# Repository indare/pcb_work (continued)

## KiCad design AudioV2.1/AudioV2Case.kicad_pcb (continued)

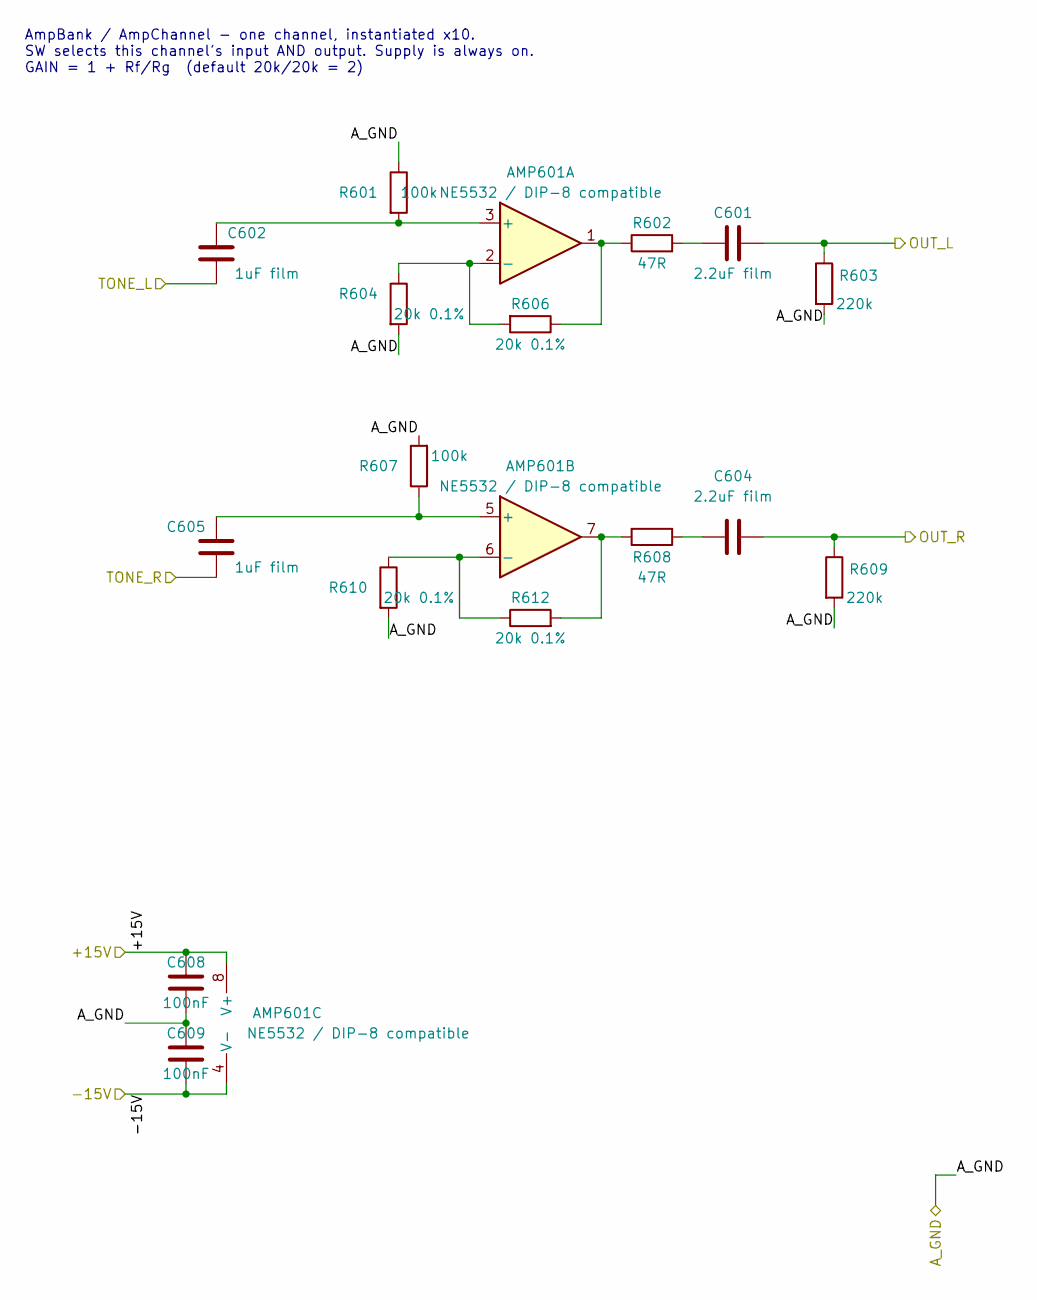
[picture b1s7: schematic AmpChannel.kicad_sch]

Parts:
AMP601: NE5532 / DIP-8 compatible; DIP-8_W7.62mm_Socket
C601, C604: 2.2uF film; C_Rect_L7.2mm_W7.2mm_P5.00mm_FKS2_FKP2_MKS2_MKP2
C602, C605: 1uF film; C_Rect_L7.2mm_W4.5mm_P5.00mm_FKS2_FKP2_MKS2_MKP2
C608, C609: 100nF; C_1206_3216Metric_Pad1.33x1.80mm_HandSolder
R601, R607: 100k; R_1206_3216Metric_Pad1.30x1.75mm_HandSolder
R602, R608: 47R; R_1206_3216Metric_Pad1.30x1.75mm_HandSolder
R603, R609: 220k; R_1206_3216Metric_Pad1.30x1.75mm_HandSolder
R604, R606, R610, R612: 20k 0.1%; R_0805_2012Metric_Pad1.20x1.40mm_HandSolder

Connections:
/+15V: AMP601.8 (V+), C608.1; also elsewhere on the board
/-15V: AMP601.4 (V-), C609.2; also elsewhere on the board
/A_GND: C608.2, C609.1, R601.1, R603.2, R604.2, R607.2, R609.2, R610.2; also elsewhere on the board
/AmpBankSwitch/CH1_OUT_L: C601.2, R603.1; also elsewhere on the board
/AmpBankSwitch/CH1_OUT_R: C604.1, R609.1; also elsewhere on the board
/TONE_L: C602.1; also elsewhere on the board
/TONE_R: C605.1; also elsewhere on the board
unnamed: AMP601.1, R602.1, R606.1
unnamed: AMP601.7, R608.2, R612.2
unnamed: AMP601.3 (+), C602.2, R601.2
unnamed: AMP601.2 (-), R604.1, R606.2
unnamed: AMP601.5 (+), C605.2, R607.1
unnamed: AMP601.6 (-), R610.1, R612.1
unnamed: C601.1, R602.2
unnamed: C604.2, R608.1

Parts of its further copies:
AMP701, AMP801, AMP901, AMP1001, AMP1101, AMP1201, AMP1301: NE5532 / DIP-8 compatible; DIP-8_W7.62mm_Socket
C701, C704, C801, C804, C901, C904, C1001, C1004, C1101, C1104, C1201, C1204, C1301, C1304: 2.2uF film; C_Rect_L7.2mm_W7.2mm_P5.00mm_FKS2_FKP2_MKS2_MKP2
C702, C705, C802, C805, C902, C905, C1002, C1005, C1102, C1105, C1202, C1205, C1302, C1305: 1uF film; C_Rect_L7.2mm_W4.5mm_P5.00mm_FKS2_FKP2_MKS2_MKP2
C708, C709, C808, C809, C908, C909, C1008, C1009, C1108, C1109, C1208, C1209, C1308, C1309: 100nF; C_1206_3216Metric_Pad1.33x1.80mm_HandSolder
R701, R707, R801, R807, R901, R907, R1001, R1007, R1101, R1107, R1201, R1207, R1301, R1307: 100k; R_1206_3216Metric_Pad1.30x1.75mm_HandSolder
R702, R708, R802, R808, R902, R908, R1002, R1008, R1102, R1108, R1202, R1208, R1302, R1308: 47R; R_1206_3216Metric_Pad1.30x1.75mm_HandSolder
R703, R709, R803, R809, R903, R909, R1003, R1009, R1103, R1109, R1203, R1209, R1303, R1309: 220k; R_1206_3216Metric_Pad1.30x1.75mm_HandSolder
R704, R706, R710, R712, R804, R806, R810, R812, R904, R906, R910, R912, R1004, R1006, R1010, R1012, R1104, R1106, R1110, R1112, R1204, R1206, R1210, R1212, R1304, R1306, R1310, R1312: 20k 0.1%; R_0805_2012Metric_Pad1.20x1.40mm_HandSolder

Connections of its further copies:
/+15V: AMP701.8 (V+), AMP801.8 (V+), AMP901.8 (V+), AMP1001.8 (V+), AMP1101.8 (V+), AMP1201.8 (V+), AMP1301.8 (V+), C708.1, C808.1, C908.1, C1008.1, C1108.1, C1208.1, C1308.1; also elsewhere on the board
/-15V: AMP701.4 (V-), AMP801.4 (V-), AMP901.4 (V-), AMP1001.4 (V-), AMP1101.4 (V-), AMP1201.4 (V-), AMP1301.4 (V-), C709.2, C809.2, C909.2, C1009.2, C1109.2, C1209.2, C1309.2; also elsewhere on the board
/A_GND: C708.2, C709.1, C808.2, C809.1, C908.2, C909.1, C1008.2, C1009.1, C1108.2, C1109.1, C1208.2, C1209.1, C1308.2, C1309.1, R701.1, R703.2, R704.2, R707.2, R709.2, R710.2, R801.1, R803.2, R804.2, R807.2, R809.2, R810.2, R901.1, R903.2, R904.2, R907.2, R909.2, R910.2, R1001.1, R1003.2, R1004.2, R1007.2, R1009.2, R1010.2, R1101.1, R1103.2, R1104.2, R1107.2, R1109.2, R1110.2, R1201.1, R1203.2, R1204.2, R1207.2, R1209.2, R1210.2, R1301.1, R1303.2, R1304.2, R1307.2, R1309.2, R1310.2; also elsewhere on the board
/AmpBankRelay/CH1_OUT_L: C1001.2, R1003.1; also elsewhere on the board
/AmpBankRelay/CH1_OUT_R: C1004.1, R1009.1; also elsewhere on the board
/AmpBankRelay/CH2_OUT_L: C1101.2, R1103.1; also elsewhere on the board
/AmpBankRelay/CH2_OUT_R: C1104.1, R1109.1; also elsewhere on the board
/AmpBankRelay/CH3_OUT_L: C1201.2, R1203.1; also elsewhere on the board
/AmpBankRelay/CH3_OUT_R: C1204.1, R1209.1; also elsewhere on the board
/AmpBankRelay/CH4_OUT_L: C1301.2, R1303.1; also elsewhere on the board
/AmpBankRelay/CH4_OUT_R: C1304.1, R1309.1; also elsewhere on the board
/AmpBankSwitch/CH2_OUT_L: C701.2, R703.1; also elsewhere on the board
/AmpBankSwitch/CH2_OUT_R: C704.1, R709.1; also elsewhere on the board
/AmpBankSwitch/CH3_OUT_L: C801.2, R803.1; also elsewhere on the board
/AmpBankSwitch/CH3_OUT_R: C804.1, R809.1; also elsewhere on the board
/AmpBankSwitch/CH4_OUT_L: C901.2, R903.1; also elsewhere on the board
/AmpBankSwitch/CH4_OUT_R: C904.1, R909.1; also elsewhere on the board
/TONE_L: C702.1, C802.1, C902.1, C1002.1, C1102.1, C1202.1, C1302.1; also elsewhere on the board
/TONE_R: C705.1, C805.1, C905.1, C1005.1, C1105.1, C1205.1, C1305.1; also elsewhere on the board
unnamed: AMP701.1, R702.1, R706.1
unnamed: AMP701.7, R708.2, R712.2
unnamed: AMP701.3 (+), C702.2, R701.2
unnamed: AMP701.2 (-), R704.1, R706.2
unnamed: AMP701.5 (+), C705.2, R707.1
unnamed: AMP701.6 (-), R710.1, R712.1
unnamed: AMP801.1, R802.1, R806.1
unnamed: AMP801.7, R808.2, R812.2
unnamed: AMP801.3 (+), C802.2, R801.2
unnamed: AMP801.2 (-), R804.1, R806.2
unnamed: AMP801.5 (+), C805.2, R807.1
unnamed: AMP801.6 (-), R810.1, R812.1
unnamed: AMP901.1, R902.1, R906.1
unnamed: AMP901.7, R908.2, R912.2
unnamed: AMP901.3 (+), C902.2, R901.2
unnamed: AMP901.2 (-), R904.1, R906.2
unnamed: AMP901.5 (+), C905.2, R907.1
unnamed: AMP901.6 (-), R910.1, R912.1
unnamed: AMP1001.1, R1002.1, R1006.1
unnamed: AMP1001.7, R1008.2, R1012.2
unnamed: AMP1001.3 (+), C1002.2, R1001.2
unnamed: AMP1001.2 (-), R1004.1, R1006.2
unnamed: AMP1001.5 (+), C1005.2, R1007.1
unnamed: AMP1001.6 (-), R1010.1, R1012.1
unnamed: AMP1101.1, R1102.1, R1106.1
unnamed: AMP1101.7, R1108.2, R1112.2
unnamed: AMP1101.3 (+), C1102.2, R1101.2
unnamed: AMP1101.2 (-), R1104.1, R1106.2
unnamed: AMP1101.5 (+), C1105.2, R1107.1
unnamed: AMP1101.6 (-), R1110.1, R1112.1
unnamed: AMP1201.1, R1202.1, R1206.1
unnamed: AMP1201.7, R1208.2, R1212.2
unnamed: AMP1201.3 (+), C1202.2, R1201.2
unnamed: AMP1201.2 (-), R1204.1, R1206.2
unnamed: AMP1201.5 (+), C1205.2, R1207.1
unnamed: AMP1201.6 (-), R1210.1, R1212.1
unnamed: AMP1301.1, R1302.1, R1306.1
unnamed: AMP1301.7, R1308.2, R1312.2
unnamed: AMP1301.3 (+), C1302.2, R1301.2
unnamed: AMP1301.2 (-), R1304.1, R1306.2
unnamed: AMP1301.5 (+), C1305.2, R1307.1
unnamed: AMP1301.6 (-), R1310.1, R1312.1
unnamed: C701.1, R702.2
unnamed: C704.2, R708.1
unnamed: C801.1, R802.2
unnamed: C804.2, R808.1
unnamed: C901.1, R902.2
unnamed: C904.2, R908.1
unnamed: C1001.1, R1002.2
unnamed: C1004.2, R1008.1
unnamed: C1101.1, R1102.2
unnamed: C1104.2, R1108.1
unnamed: C1201.1, R1202.2
unnamed: C1204.2, R1208.1
unnamed: C1301.1, R1302.2
unnamed: C1304.2, R1308.1

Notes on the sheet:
AmpBank / AmpChannel - one channel, instantiated x10. SW selects this channel's input AND output. Supply is always on. GAIN = 1 + Rf/Rg (default 20k/20k = 2)

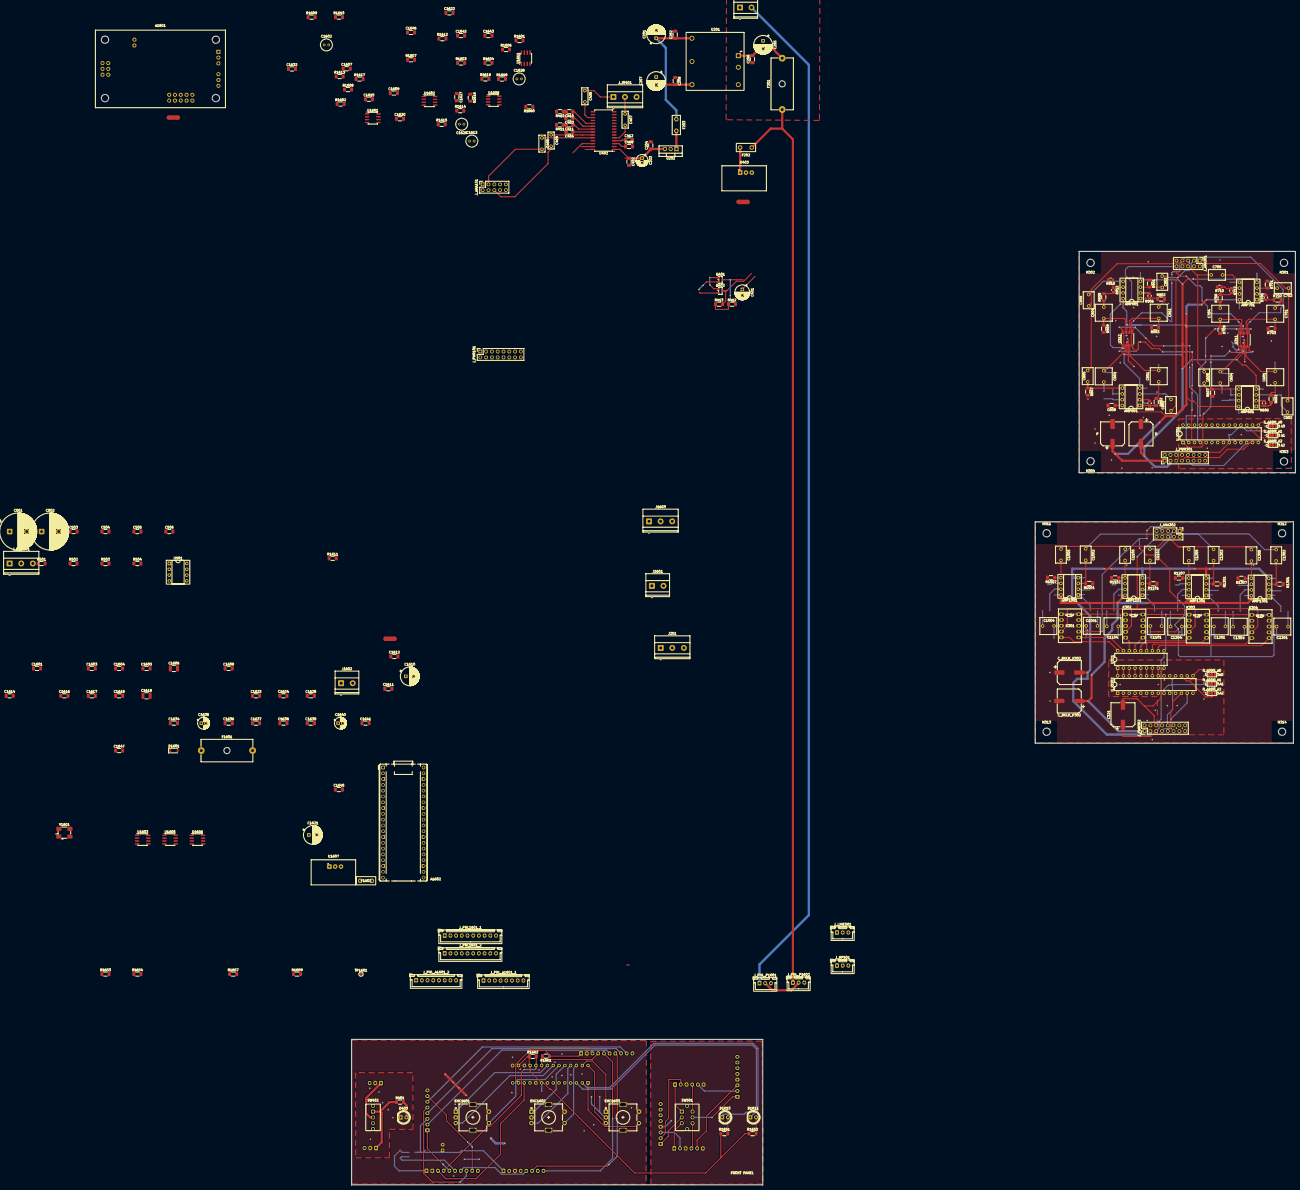
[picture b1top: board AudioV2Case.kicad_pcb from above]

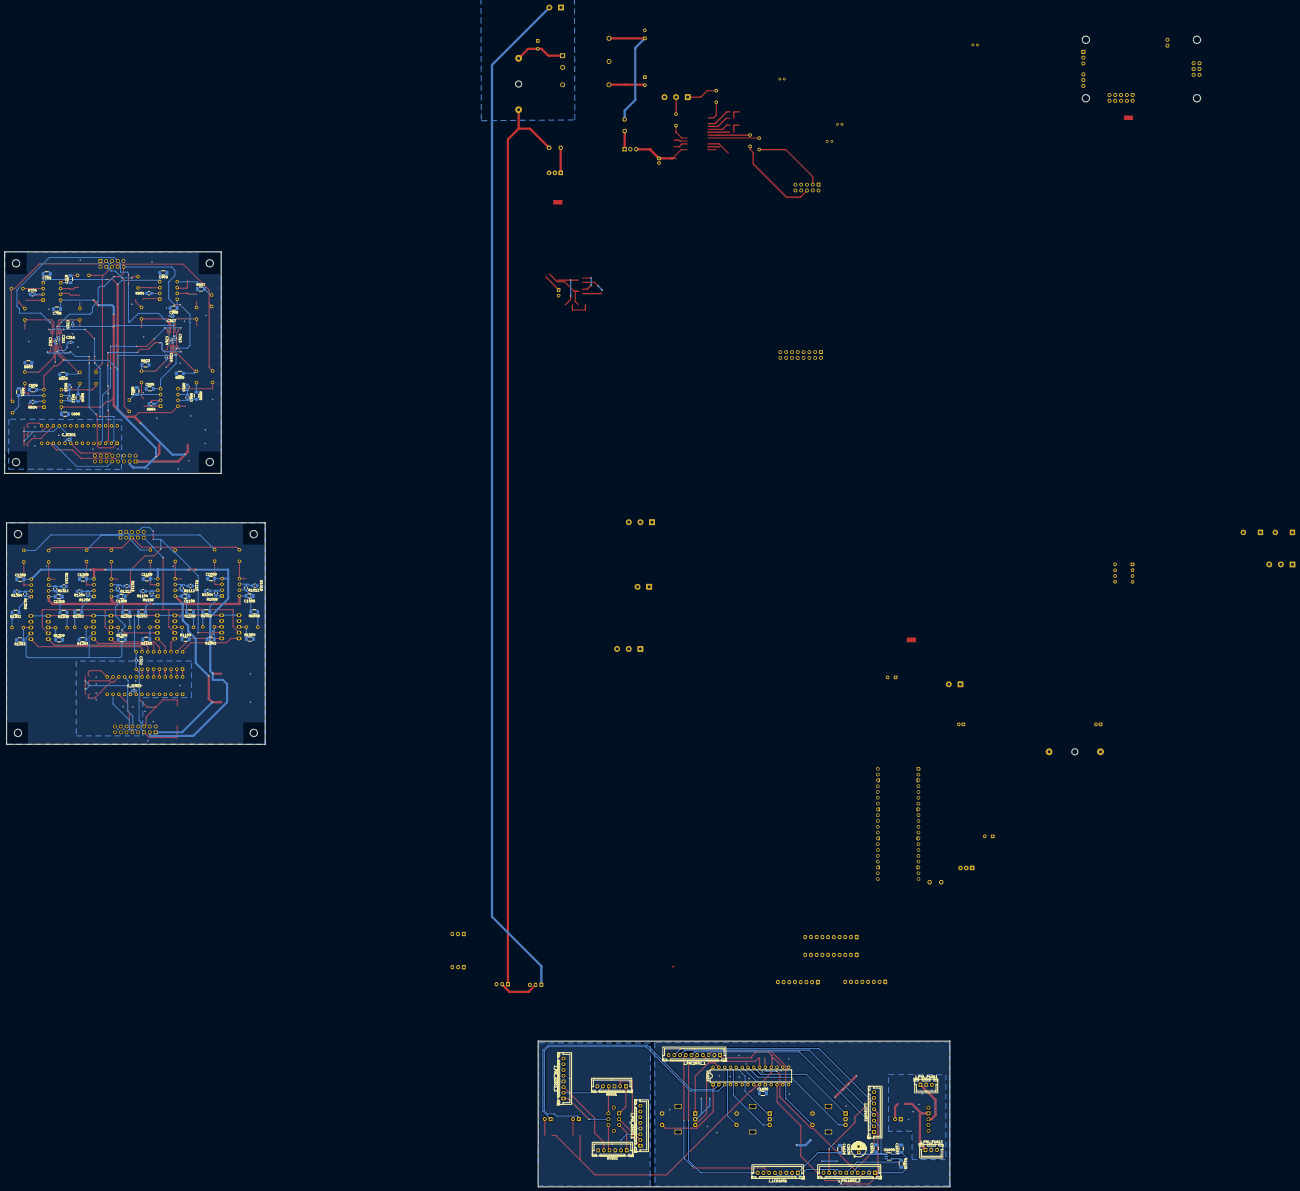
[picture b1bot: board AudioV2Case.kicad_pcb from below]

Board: 2 copper layers, 355 parts (94 on the bottom side), 225 nets.

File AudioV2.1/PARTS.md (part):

# AudioV2.1 品番（回路から決めた第一候補）

**目的:** 回路が要求する電気・機械条件から型番を決める。在庫は変動するので **機能等価の代替** を併記する。
決定とその理由は [DECISIONS.md](DECISIONS.md)。ここは品番・調達・実装の置き場。

**実装の型:** RV / SW_DEST / ENC / PWR SW は **パネル実装**（操作系は FrontPanel 子基板に集約）。

> **この文書の読み方 — どこが生成で、どこが手書きか**
>
> `<!-- BEGIN GENERATED: ... -->` 〜 `<!-- END GENERATED: ... -->` で囲まれたブロックは
> **回路図から自動生成**したもの（§4.1 の部品表）。
> **手で編集しても次の再生成で消える。** 直すときは KiCad の回路図側を直して再生成する。
>
> それ以外はすべて**手書きで、こちらが正**。調達先・代替品・選定理由など、**回路図から導出できない情報**を置く場所。
> 手書きの部分は 2026-09-25 の図（v2 から写した状態）に合わせてある。v2.1 の変更（RS6・リレー・LDO など）を図に入れたら、品番もここへ足す。
>
> ```bash
> python3 AudioV2.1/scripts/gen_parts_bom.py          # 再生成して埋め込み直す
> python3 AudioV2.1/scripts/gen_parts_bom.py --check  # 実図とズレていれば非ゼロ終了（検査のみ）
> ```

---

## 0a. 何を繋ぐか（**2026-09-06 確定。バッファの設計はここで決まる**）

**出力段の設計は「先に何を繋ぐか」で決まる**のに、それがどこにも書かれていなかった。ユーザー確定分:

| 出口 | 繋ぐもの | 公称仕様 | 出典 |
|---|---|---|---|
| **PHONE** | **Sennheiser HD 560S** | **120 Ω** / 110 dB SPL/V @1 kHz | メーカー公称（**二次情報**。データシート PDF ではない） |
| **PHONE** | **HyperX Cloud III** | **64 Ω** / 100 dB SPL/mW @1 kHz | 同上 |
| **LINE** | **IK Multimedia iLoud Micro Monitor** | RCA 不平衡 ＋ TRS 1/8" 平衡。**⚠ 入力インピーダンスと入力感度はメーカーが公表していない**（仕様ページは出力特性のみ） | メーカー仕様ページ |

**⚠ 32 Ω 級は無い。** 「32 Ω の低能率を駆動する」という前提で部品を選ばないこと
（v1 の `NJM4556A` 70 mA 級はその前提で選ばれたと思われる）。

**⚠ `iLoud` の入力インピーダンスが不明なのは、ライン出力バッファの要否に直結する。**
`A50k` ポットのワイパーは電気的中点で `Zout` 最大 12.5 kΩ。負荷による追加損失は
**10 kΩ で −7.0 dB / 20 kΩ で −4.2 dB / 47 kΩ で −2.1 dB**（`600 Ω` なら −26.8 dB）。
**アクティブモニタの RCA は 10〜47 kΩ 級が普通**なので、**この範囲なら「損失」ではなく
「A カーブが崩れてつまみの位置が変わる」だけ**で、上に 10 dB 以上の余裕がある以上、実害は小さい。
**測定用途で「つまみを動かすと 20 kHz の応答が動く」ことを嫌うなら、バッファを入れる理由になる。**

---

## 0b. ベンダのデータを読むときの罠（実際に踏んだもの）

価格・在庫は変動するので**スナップショットは残さない**。代わりに読み方を残す。
すべて 2026-09-02 の DC-DC 選定（v2 のとき）で実際に踏んだもの。

| 罠 | どうする |
|---|---|
| **通貨単位** | 当時の価格表が **¥ と $ を取り違えていた**（`¥9.98` と書かれた値の実体は **¥1,581**）。桁が3つ違っても表の中では気づかない。**通貨を明示していない数字を比較に使わない** |
| **MOQ（最小注文数量）** | `UnitPrice` だけで並べると**順位を間違える**。MOQ 19（チューブ）の品は単価最安でも実際に払うのは 19 個分。**「最低購入額 = 単価 × MOQ」で並べる**。API では `ProductVariations[].MinimumOrderQuantity` |
| **包装で品番が分かれる** | 同じ石でもカットテープ / テープ&リール / Digi-Reel で別品番になり、**テープ&リールは MOQ 3000・在庫0**、Digi-Reel は別途リール手数料。**買うのはカットテープ（`...CT-ND`）** |
| **入手性フィールド** | **DigiKey API の入手性フィールドは信用できない**（`AM10TW` で判明。正規ルートから消えているのに在庫ありに見えた）。在庫の判断は実ページで確認する。**⚠ ただし実ページが見られない環境では下の「販売元」を使う** |
| **販売元（Marketplace か直販か）** | **`ProductUrl` のスラグが `Manufacturer.Name` と食い違ったら Marketplace 出品**。DigiKey の商品 URL は `/products/detail/<メーカのスラグ>/<型番>/<id>` なので、両者は普通一致する。**2026-09-05 に 1023 件で試したら不一致は `aimtec → dcomponents` の 25 件だけで、うち 22 件が `BackOrderNotAllowed=True`。** 記録にある `AM10TW` の在庫誤認はこれ —— **在庫を持っていたのは DigiKey ではなく出品者**だった。`MarketPlace` フィールド自体は `None` を返すので役に立たない。**`www.digikey.com` が塞がっている環境でも、この判別は API だけでできる** |
| **`ProductStatus`** | **「新規設計向けに不適合」(NFND) は候補から即落とす。** 性能で比べる前に見ること。2026-09-05 の再探索では `URA2412ZP-10WR3`（Mornsun）と `PYBE10-Q24-D12`（Bel）がこれで、**どちらも `NormallyStocking=False` かつ `BackOrderNotAllowed=True`**。データシートを読む手間ごと省ける |
| **属性 vs データシート** | DigiKey の属性が**データシートと矛盾する**ことがある（`REC10K` の絶縁は属性 3 kV / DS は **1.6 kVDC**）。**データシートを正とする** |
| **足切りは価格ではない** | DC-DC の決め手は価格ではなく **最大容量負荷 Cout** だった。**回路が課す制約（§0）で先に落とす**、価格で並べるのはその後 |

探索そのものは [`scripts/dcdc_survey.py`](scripts/dcdc_survey.py) / [`scripts/digikey_search.py`](scripts/digikey_search.py) で再実行できる。
**ライブ API を叩くので結果は当時と変わる** — 変わってよい。固定したいのは上の読み方だけ。

---

## 0c. 受動部品の調達クラス（PRECISION / MATCH / SPEC）— [issue #38](https://github.com/indare/pcb_work/issues/38)

この箱はオペアンプ以外の部品差が比較結果へ混入しないことが大事。
**高価な部品を目的にしない。** 比較チャネル間の再現性・対称性を優先する。

| クラス | やり方 | いつ使う |
|---|---|---|
| **PRECISION** | メーカ公差で性能を保証。個体選別はしない | 公差がそのままチャネル差になる抵抗など。低コストで 0.1% が買えるとき |
| **MATCH** | 同一シリーズを必要数より多く買い、LCR で実測選別 | 公称公差が ±5〜20% でも個体差が大きいコンデンサなど。「公称に近い」より「互いが近い」 |
| **SPEC** | 回路上必要な仕様を満たせば個体選別しない | デカップ・電源バルク・プルアップ／プルダウン・LED 抵抗など |

計測器は **周波数指定できる LCR メータ**（例: DER EE DE-5000）。TC-1 は選別の主器にしない。
必要なら ZT-703S＋正弦波で実回路の周波数応答を確認する。

### PRECISION（確定）

| 役割 | 値 | 方針 |
|---|---|---|
| AmpChannel `Rf` / `Rg` | **20 kΩ 0.1%**（薄膜、図上 Value も `20k 0.1%`） | ch 間ゲインの支配項。1%→0.174 dB、0.1%→0.017 dB。候補例: Susumu `RG2012` 系（FP は図の 0805）。ADC 前段の 0.1% と同じクラス |
| ADC 前段抵抗 | 既に図上 `… 0.1%` | 据え置き |

### MATCH（確定）

同一ロット／同一シリーズを多めに買い、**同一測定周波数**で C（必要なら ESR / D）を揃える。
絶対値より個体間一致を優先。目安: 必要数の **2〜3 倍**を買い、近い個体を実装。

| 役割 | シリーズ／条件 | 選別 |
|---|---|---|
| AmpChannel 入力カップリング **1 µF film** | **PET（MKT）・P5**。採用: TDK `B32529C0105J000`。FP は図どおり L7.2/W4.5/P5。PP は歪み差が見えず巨大になるので採らない（v2 で決めた） | C 一次 → D/ESR 二次確認 |
| AmpChannel 出力カップリング **2.2 µF film** | 同系統 TDK `B32529D0225…`（P5）。FP は L7.2/W7.2/P5。公称 ±5〜10% で足りるが、**低域カットオフ差は容量差そのもの**なので選別する | 同上 |
| ADC LPF **1.8 nF C0G** | C0G/NP0・1206。公称 ±5% 級を買い、**ch / L/R で C を揃える** | C @ 同一周波数 |
| HP 出力 **470 µF NP** | Muse ES `UES1E471MHM` 想定（Ø16/P7.5）。**L/R をペア選別** | C + ESR |
| ADC 信号経路の **10 µF NP** | 左右対称が目的のカップリング | C で L/R を揃える |

### SPEC（据え置き）

100 nF デカップ、電源バルク、プルアップ／プルダウン、LED 抵抗など。
耐圧・ESR・寿命・温度など、用途ごとのデータシート条件を優先。個体選別しない。

---

## 2. パネル部品と周辺の第一候補

### 2.1 SW_DEST / PWR SW — **Cosland 2MD1 / 2MS1**

| | |
|---|---|
| DEST | **Cosland 2MD1**（DPDT ON–ON、秋月 104028）。PHONE↔LINE の 1 本。MUTE 位置は無い（DECISIONS `V21-継-04`） |
| PWR | **Cosland 2MS1**（秋月 100300）。片側 NC で ON–OFF として使う |
| FP | `Library:SW_Toggle_Cosland_2MD1_VS2_DPDT`／`Library:SW_Toggle_Cosland_2MS1_VS2_SPDT` |

### 2.2 RV_HP / RV_LINE — **Alps RK27112A00CF** ×2

| | |
|---|---|
| 機能 | **A（対数）50 kΩ デュアル**、カーボン、1 回転 |
| 外形 | RK27 **27 mm**、軸 φ6 × 20 mm、取付 M9 |
| 電力 | 0.05 W — 本回路の ~1 mW に対し十分 |
| ギャング誤差 | DS 目安 2 dB（-60〜0 dB）— ステレオ音量として実用 |
| 実装 | **パネル**。ポット本体はユニバーサル基板から `JST XH 6P` で FrontPanel へ（`Device:R_Potentiometer_Dual` のピン番号のまま） |
| なぜ RK097 でないか | v1 は RK097 水平実装。この箱は **ノブを主操作子**にするので 27 mm を第一にする |

**代替**

| 状況 | 内容 |
|---|---|
| RK27 欠品・高い | パネル用 **A50k デュアル**ならピン互換で可（台湾 Alpha RD901 系など）。カーブが **A** であること |
| v1 と見た目を揃える | Alps **RK097 デュアル A50k**（水平ピン）。9 mm で「目立たない」。回路は同一 |
| A100k | 可。中点 Zout が上がるので **A50k 優先** |

RK097 のカタログ現役は 10 kΩ デュアルが多く、**A50k デュアルは RK27 の方が型番が取りやすい**。

### 2.3 その他・回路上まだ曖昧だったもの

| 用途 | 第一候補 | 理由 |
|---|---|---|
| **ENC×3** | 秋月 **EC11 系・押し SW 付き**（D カット、固定足東西） | DECISIONS `V21-継-01`。PPR は CH/Bass/Treble では何周でも可。購入品の寸法で FP を切る |
| **操作 Pico** | **Raspberry Pi Pico 2**（RP2350、**W なし**、SC0915 相当） | Wi-Fi 不要。ヘッダ後付け可 |
| **LCD（スペアナ）** | **Waveshare 29318**（スイッチサイエンス [10138](https://www.switch-science.com/products/10138)） | v1 の計測器と同じ LCD。ST7796S SPI + FT6336U I²C。状態表示（CH / DEST / Bass / Treble）もここへ寄せた（OLED は無い） |
| **12 V LED** | **12 V 内蔵抵抗付き 5 mm**（緑または青、~10 mA） | 素 LED なら 680 Ω–1 kΩ |
| **DEST LED×2** | 3 mm 通常 LED（Vf≈2 V）+ 既存 **1 kΩ** | 3.3 V で ~1.3 mA。暗ければ 330 Ω に落とす |
| **AZ850** | **AZ850P2-5**（秋月 118017） | コイル **5 V** / 125 Ω / ~40 mA。`TBD62083APG` + BP5293-50 と一致。**12 V コイルは使わない**。電源は母板の `BP5293-50` が `PD_12V_SW` から作る **`+5V_COIL`** で、帰路は専用の `GND_COIL`（`NT101` で1点結合）。娘基板側に 100 µF + 100 nF のローカルバイパスがあるので、パルスとフライバックは娘基板内で閉じる |
| **MCP23017** | **`MCP23017-E/SP`**（DIP-28） | UI 側は 0x22。娘の番地はジャンパ（今の図の形。v2.1 で娘の MCP を残すかは V21-未決-03）。**個数は回路図から導出できるので §4.1 の部品表を見る** |
| **DIP-28 ソケット** | **板バネ（dual-wipe）型**、28 pos / 行間隔 0.300"（7.62 mm） | 挿さるのは `MCP23017` だけ＝ I²C のデジタルなので接触抵抗も歪みも効かない。品番は発注時（DECISIONS `V21-継-12`） |
| **リレードライバ** | **`TBD62083APG`**（DIP-18。`ULN2803` とピン互換） | **`ULN2803` は不採用**（D24）。ダーリントンの約 1 V 降下では 40 ℃ 超で `AZ850` の Must Operate を満たさない。DMOS なら 40 mA で 0.13 V |
| **PT2314E** | **PT2314E SOP-28 300 mil**（回路値 `PT2314E`） | 無印 DIP は入手不可。2026-09-07 に E へ確定（DECISIONS `V21-継-05`） |
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
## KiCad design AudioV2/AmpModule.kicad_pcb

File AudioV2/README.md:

# AudioV2

**「オペアンプを何個も電子的に切り替えて、なんとなく音が違うのを楽しむ箱」の KiCad プロジェクト。**
計測系が載っているのは「切替素子が音を悪くしないか」を確かめるためで、装置そのものは計測器ではない。
優劣は測定ではなく耳で決める。

母板に電源・トーン・出力段をまとめ、オペアンプと切替素子を載せた**娘基板をヘッダでスタック**する。
娘基板は切替素子だけを替えた版を作り、**同じ箱に混ぜて挿して同一セッションで比べる**
（時間ドリフトと抜き差しを比較に交絡させないため）。**PCB は未着手。**

この段落より詳しいことは以下の文書が正。**README には書かない。**

## 着手する前に読むもの

| | 何が書いてあるか |
|---|---|
| [`../CLAUDE.md`](../CLAUDE.md) | **守ること。シートの所有権**（どれをスクリプトが生成し、どれを KiCad で直すか）**と検証コマンド・その期待値** |
| [`../SOURCE_OF_TRUTH.md`](../SOURCE_OF_TRUTH.md) | ドキュメントに何を書き、何を書かないか。**ドキュメント編集の前に必読** |
| [AGENT_HANDOFF.md](AGENT_HANDOFF.md) | 長い文脈の入口。確定事項の一覧・次にやること・踏んだ落とし穴 |

回路図のシート構成と、手で触ってよいシートは **`CLAUDE.md` の所有権表が正**。
構成は何度も変わっているので、ここには写さない。

## この下にあるもの

| | |
|---|---|
| `*.kicad_sch` / `AudioV2.kicad_sym` / `AudioV2Case.kicad_pro` | 回路図本体。`AudioV2Case.kicad_pcb` は空のスキャフォールド（PCB 未着手） |
| [DECISIONS.md](DECISIONS.md) | **確定事項の正。** 電源レール・切替方式・基板構成・スタック規格。迷ったらここ |
| [CIRCUIT_DESIGN.md](CIRCUIT_DESIGN.md) | 回路の構成、データシートとのピン照合、机上検算 |
| [PARTS.md](PARTS.md) | 品番と機能等価の代替。BOM のブロックは回路図から生成する |
| [WIRING.md](WIRING.md) | 箱配線・シールドの落とし方・図の外にある流用基板との接続 |
| [DEST_SENSE_LADDER.md](DEST_SENSE_LADDER.md) | 出力先センスの抵抗ラダー設計 |
| [spice/](spice/README.md) | 設計判断の根拠に回した ngspice ネットリスト |
| [scripts/](scripts/) | 回路図の生成・編集・検証の道具。どれを何に使うかは `CLAUDE.md` |
| [datasheets/](datasheets/) | 参照したデータシート PDF |
| [legacy/](legacy/README.md) | **母板へ統合済みの旧シート。凍結してある。編集しても設計には反映されない** |
| 発注リスト | **持たない。** 発注のときに [PARTS.md](PARTS.md) §4.1 の生成部品表から起こす。ベンダのデータを読むときの罠は §0b |
| [VOLUME_IC_COMPARISON.md](VOLUME_IC_COMPARISON.md) / [SYMBOL_FIX_TODO.md](SYMBOL_FIX_TODO.md) / [SYMBOL_REVIEW_SUMMARY.md](SYMBOL_REVIEW_SUMMARY.md) | **2026-08-30 前後の記録。** 不採用になった案・当時の作業指示で、現構成より前の内容 |

## 古い記述の読み方

構成を何度も作り直しているので、**どの文書にも日付の違う記述が混在している。**
不採用になった経路も「同じ検討を繰り返さない」ために消さずに残してある。

- **新しい日付の節が正。** 最新は [DECISIONS.md](DECISIONS.md) と
  [AGENT_HANDOFF.md](AGENT_HANDOFF.md) の確定事項に集約されている
- 解体されたシートの名前（`ControlPanel` / `PowerModule` / `OutputStage` / `RelayBoard` /
  `AmpModule` / 10ch 一体の `AmpBank`）が出てくる節は、**旧構成の記録**
- 部品数・ERC 件数・ネット名・ピン接続は**回路図が正**。文書の値は当時のもの
  （[`../SOURCE_OF_TRUTH.md`](../SOURCE_OF_TRUTH.md)）

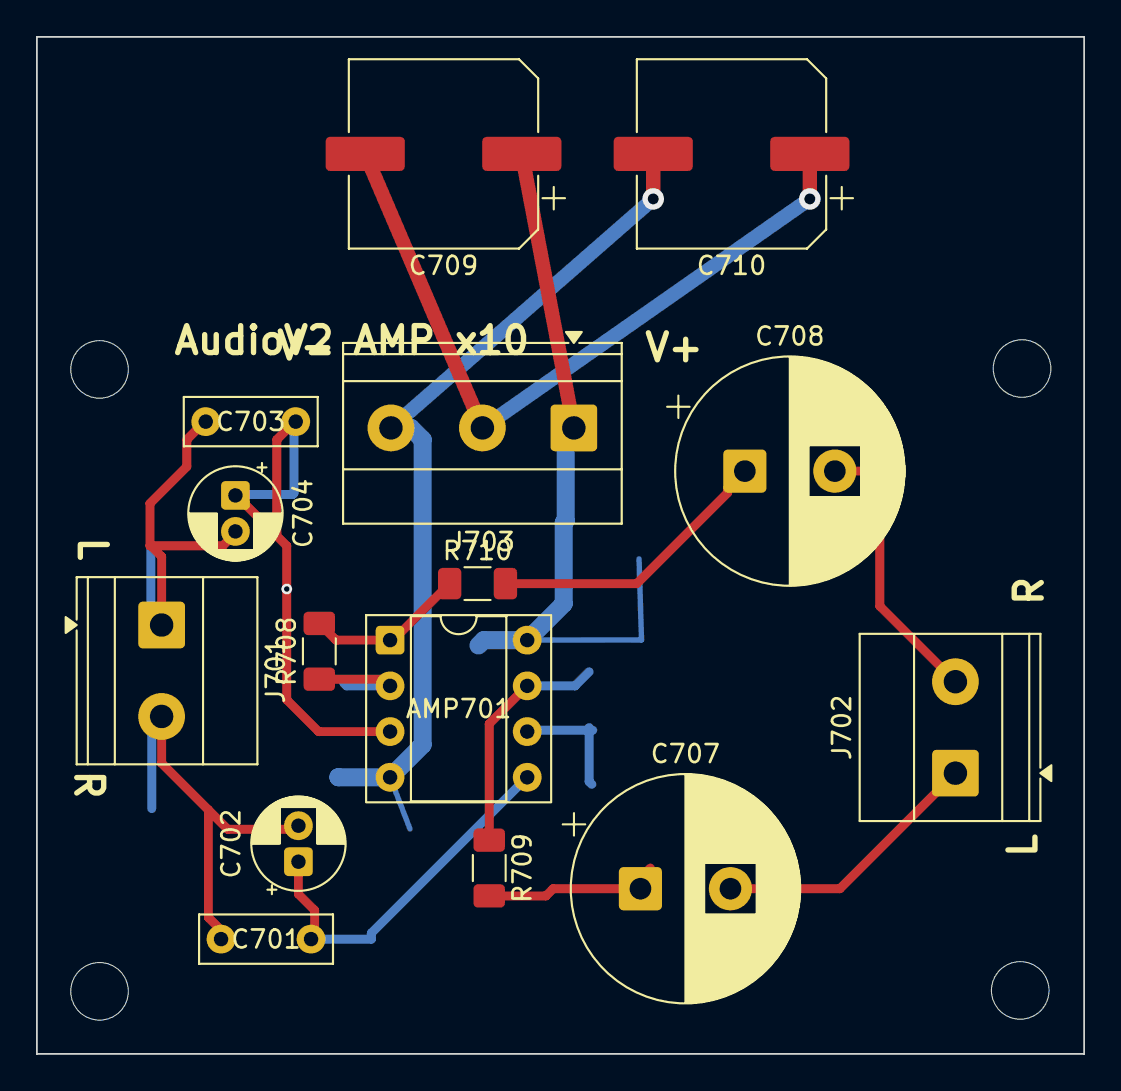
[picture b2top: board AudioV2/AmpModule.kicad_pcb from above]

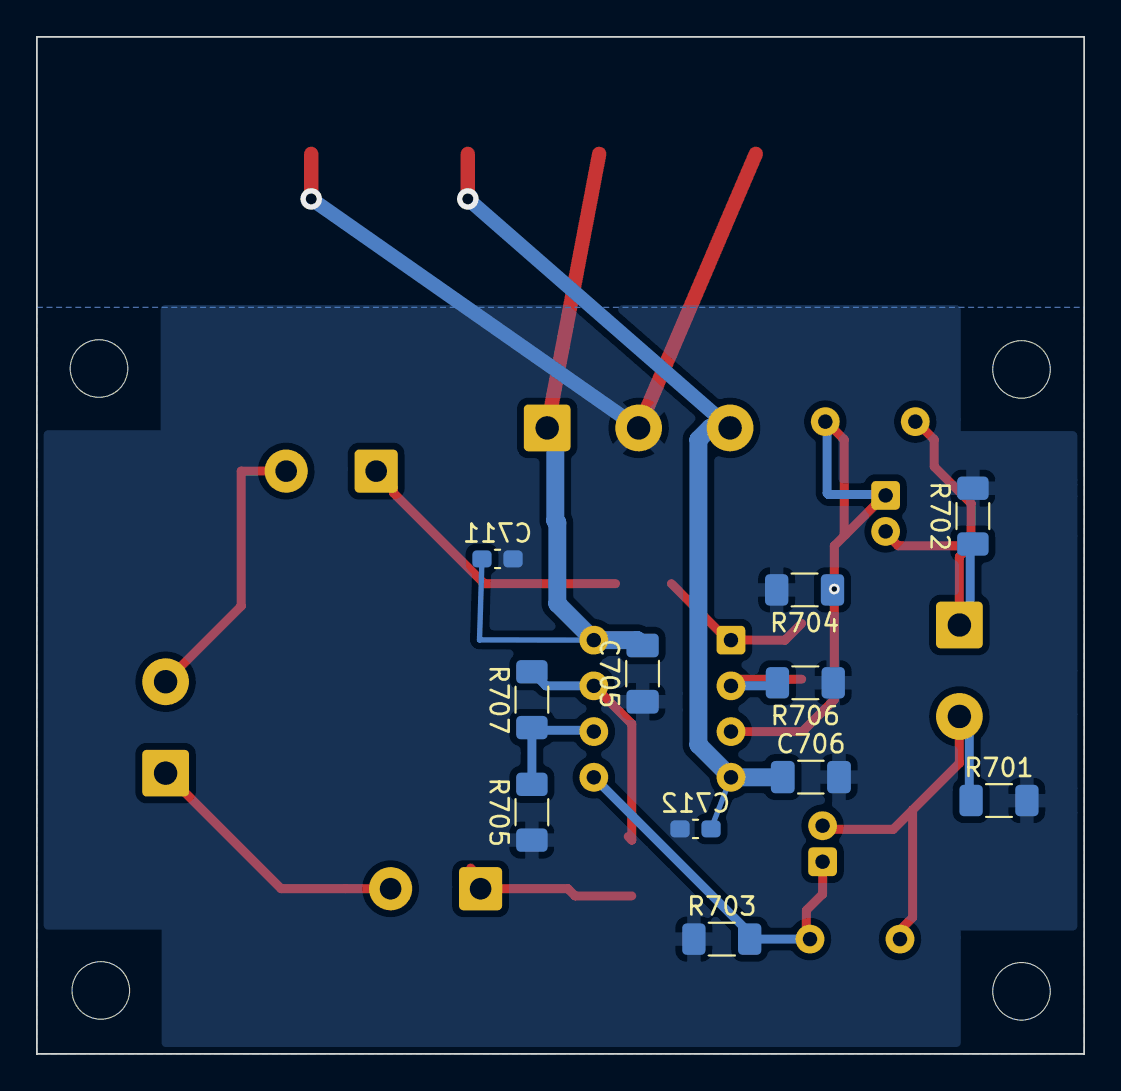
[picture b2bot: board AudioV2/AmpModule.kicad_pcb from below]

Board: 2 copper layers, 58.2 x 56.5 mm, 30 parts (11 on the bottom side), 15 nets.

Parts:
AMP701: NE5532 / DIP-8 compatible; DIP-8_W7.62mm_Socket
C701, C703: 100nF film; C_Rect_L7.2mm_W2.5mm_P5.00mm_FKS2_FKP2_MKS2_MKP2
C702, C704: 10uF; CP_Radial_D5.0mm_P2.00mm
C705, C706: 100nF 50V X7R; C_1206_3216Metric_Pad1.33x1.80mm_HandSolder
C707, C708: 470uF 25V; CP_Radial_D12.5mm_P5.00mm
C709, C710: 100uF 35V polymer; CP_Elec_10x12.6
C711, C712: 1nF 50V C0G; C_0603_1608Metric_Pad1.08x0.95mm_HandSolder
H701, H702, H703, H704: MountingHole; MountingHole_3.2mm_M3
J701: AMP_IN L/R; TerminalBlock_Phoenix_MKDS-1,5-2-5.08_1x02_P5.08mm_Horizont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
J702: AMP_OUT L/R; TerminalBlock_Phoenix_MKDS-1,5-2-5.08_1x02_P5.08mm_Horizont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
J703: +12V / A_GND / -12V; TerminalBlock_Phoenix_MKDS-1,5-3-5.08_1x03_P5.08mm_Horizont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
R701, R702: 220k; R_1206_3216Metric_Pad1.30x1.75mm_HandSolder
R703, R704: 1k; R_1206_3216Metric_Pad1.30x1.75mm_HandSolder
R705, R706, R707, R708: 20k; R_1206_3216Metric_Pad1.30x1.75mm_HandSolder
R709, R710: 47R; R_1206_3216Metric_Pad1.30x1.75mm_HandSolder

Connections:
+12V: AMP701.8 (V+), C705.2, C709.1, C711.2, J703.1
-12V: AMP701.4 (V-), C706.1, C710.2, C712.1, J703.3
A_GND: C705.1, C706.2, C709.2, C710.1, C711.1, C712.2, J703.2, R701.2, R702.2, R703.1, R704.2, R705.1, R706.1
L_AC: AMP701.5 (+), C701.1, C702.1, R703.2
L_IN: C701.2, C702.2, J701.2, R701.1
L_INV: AMP701.6 (-), R705.2, R707.1
L_OUT: C707.2, J702.1
L_OUT_OP: AMP701.7, R707.2, R709.1
L_OUT_PRE: C707.1, R709.2
R_AC: AMP701.3 (+), C703.1, C704.1, R704.1
R_IN: C703.2, C704.2, J701.1, R702.1
R_INV: AMP701.2 (-), R706.2, R708.1
R_OUT: C708.2, J702.2
R_OUT_OP: AMP701.1, R708.2, R710.1
R_OUT_PRE: C708.1, R710.2
